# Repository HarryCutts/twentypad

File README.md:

# TwentyPad
TwentyPad is a simple twenty-key macro pad, that I built to learn about PCB design.

This repository contains the KiCAD project for PCB manufacture and assembly. The case was [designed
in Onshape][onshape-proj].

[onshape-proj]: https://cad.onshape.com/documents/e1701c21a3cb18f7b5686e27/w/70a0bcde95206762f85e44bf/e/dfee6d06467dfd7de2e80397

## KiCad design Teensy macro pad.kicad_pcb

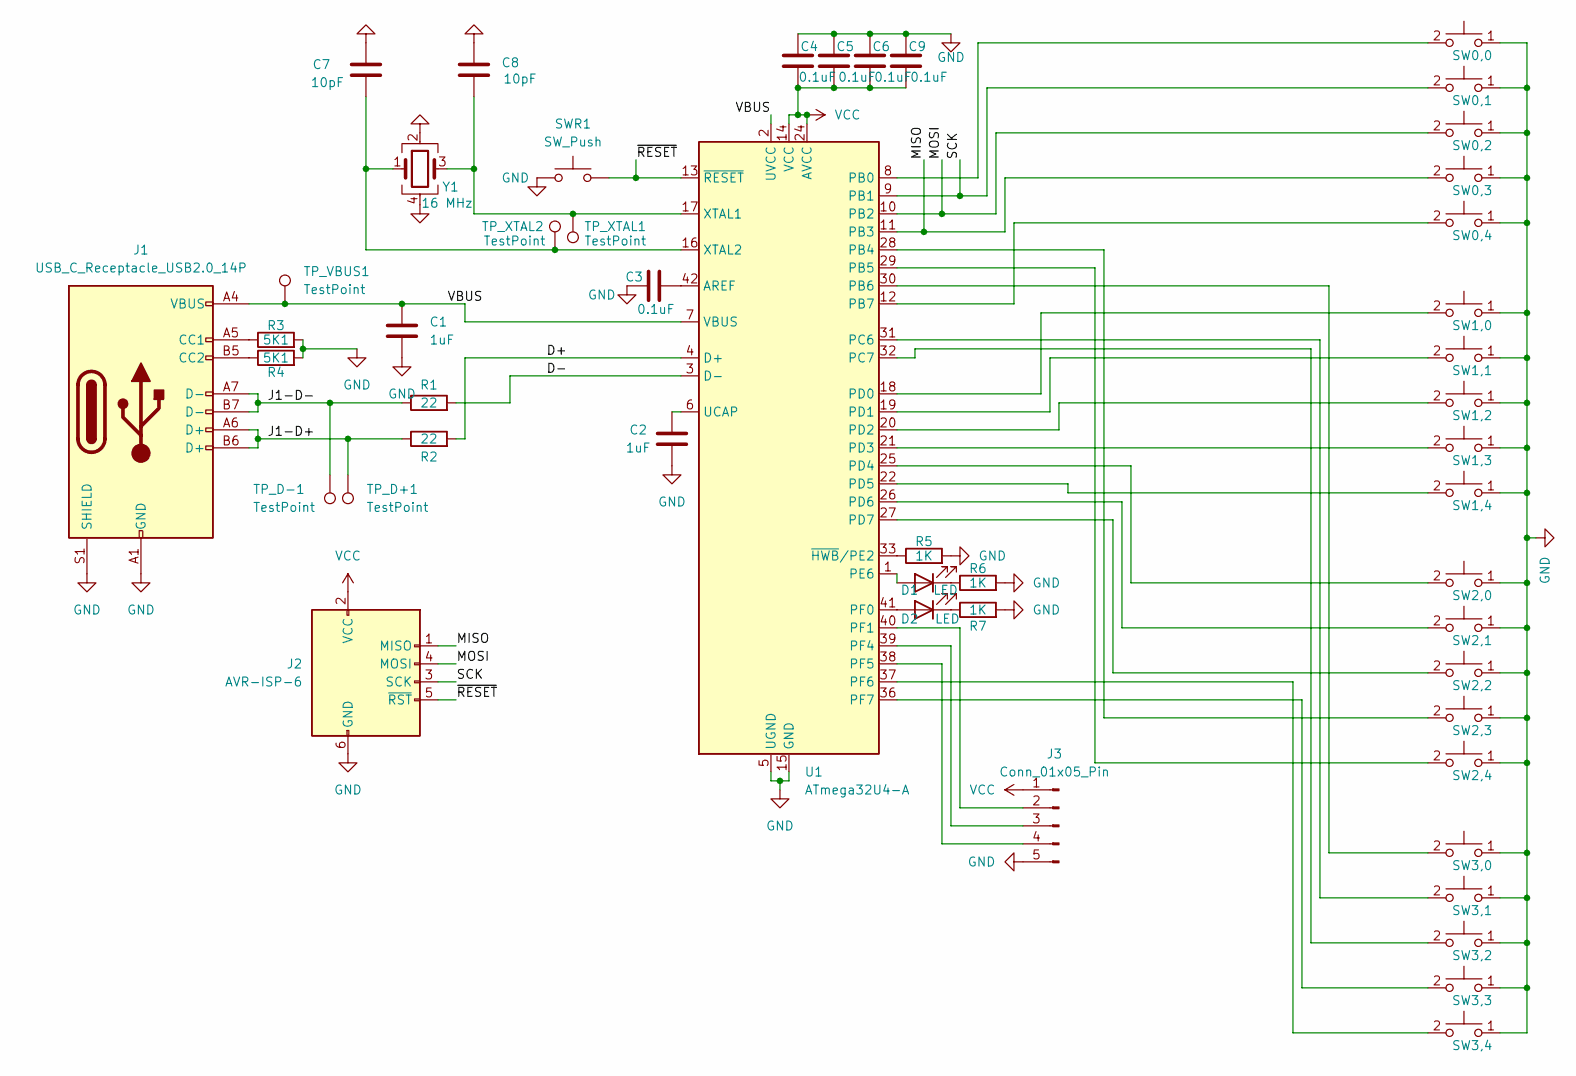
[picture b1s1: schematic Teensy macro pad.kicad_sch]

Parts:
C1, C2: 1uF; C_0805_2012Metric
C3, C4, C5, C6, C9: 0.1uF; C_0805_2012Metric
C7, C8: 10pF; C_0603_1608Metric
D1, D2: LED; LED_D5.0mm
J1: USB_C_Receptacle_USB2.0_14P; USB_C_Receptacle_HRO_TYPE-C-31-M-12
J2: AVR-ISP-6; IDC-Header_2x03_P2.54mm_Vertical
J3: Conn_01x05_Pin; PinHeader_1x05_P2.54mm_Vertical
R1, R2: 22; R_0805_2012Metric
R3, R4: 5K1; R_0805_2012Metric
R5, R6, R7: 1K; R_0805_2012Metric
SW0,0, SW0,1, SW0,2, SW0,3, SW0,4, SW1,0, SW1,1, SW1,2, SW1,3, SW1,4, SW2,0, SW2,1, SW2,2, SW2,3, SW2,4, SW3,0, SW3,1, SW3,2, SW3,3, SW3,4: CherryMX; SW_Cherry_MX_1.00u_PCB_with_bridge
SWR1: SW_Push; SW_Push_1P1T_XKB_TS-1187A
TP_D+1: TestPoint; TestPoint_Pad_D2.0mm
TP_D-1: TestPoint; TestPoint_Pad_D2.0mm
TP_VBUS1: TestPoint; TestPoint_Pad_D2.0mm
TP_XTAL1, TP_XTAL2: TestPoint; TestPoint_Pad_D2.0mm
U1: ATmega32U4-A; TQFP-44_10x10mm_P0.8mm
Y1: 16 MHz; Crystal_SMD_3225-4Pin_3.2x2.5mm

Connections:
/D+: R2.2, U1.4 (D+)
/D-: R1.2, U1.3 (D-)
/J1-D+: J1.A6 (D+), J1.B6 (D+), R2.1, TP_D+1.1
/J1-D-: J1.A7 (D-), J1.B7 (D-), R1.1, TP_D-1.1
/MISO: J2.1 (MISO), SW0,3.2, U1.11 (PB3)
/MOSI: J2.4 (MOSI), SW0,2.2, U1.10 (PB2)
/SCK: J2.3 (SCK), SW0,1.2, U1.9 (PB1)
/VBUS: C1.1, J1.A4 (VBUS), J1.A9 (VBUS), J1.B4 (VBUS), J1.B9 (VBUS), TP_VBUS1.1, U1.2 (UVCC), U1.7 (VBUS)
/~RESET: J2.5 (~RST), SWR1.2, U1.13 (~RESET)
GND: C1.2, C2.2, C3.1, C4.2, C5.2, C6.2, C7.1, C8.1, C9.2, J1.A1 (GND), J1.A12 (GND), J1.B1 (GND), J1.B12 (GND), J1.S1 (SHIELD), J2.6 (GND), J3.5, R3.2, R4.2, R5.2, R6.2, R7.2, SW0,0.1, SW0,1.1, SW0,2.1, SW0,3.1, SW0,4.1, SW1,0.1, SW1,1.1, SW1,2.1, SW1,3.1, SW1,4.1, SW2,0.1, SW2,1.1, SW2,2.1, SW2,3.1, SW2,4.1, SW3,0.1, SW3,1.1, SW3,2.1, SW3,3.1, SW3,4.1, SWR1.1, U1.5 (UGND), U1.15 (GND), U1.23 (GND), U1.35 (GND), U1.43 (GND), Y1.2, Y1.4
unnamed: D1.2 (A), U1.1 (PE6)
unnamed: D1.1 (K), R6.1
unnamed: D2.2 (A), U1.41 (PF0)
unnamed: D2.1 (K), R7.1
unnamed: J1.A5 (CC1), R3.1
unnamed: J1.B5 (CC2), R4.1
unnamed: J3.2, U1.40 (PF1)
unnamed: J3.3, U1.39 (PF4)
unnamed: J3.4, U1.38 (PF5)
unnamed: C3.2, U1.42 (AREF)
unnamed: SW0,0.2, U1.8 (PB0)
unnamed: SW2,3.2, U1.28 (PB4)
unnamed: SW2,4.2, U1.29 (PB5)
unnamed: SW3,0.2, U1.30 (PB6)
unnamed: SW0,4.2, U1.12 (PB7)
unnamed: SW3,1.2, U1.31 (PC6)
unnamed: SW3,2.2, U1.32 (PC7)
unnamed: SW1,0.2, U1.18 (PD0)
unnamed: SW1,1.2, U1.19 (PD1)
unnamed: SW1,2.2, U1.20 (PD2)
unnamed: SW1,3.2, U1.21 (PD3)
unnamed: SW2,0.2, U1.25 (PD4)
unnamed: SW1,4.2, U1.22 (PD5)
unnamed: SW2,1.2, U1.26 (PD6)
unnamed: SW2,2.2, U1.27 (PD7)
unnamed: SW3,4.2, U1.37 (PF6)
unnamed: SW3,3.2, U1.36 (PF7)
unnamed: C2.1, U1.6 (UCAP)
unnamed: C8.2, TP_XTAL1.1, U1.17 (XTAL1), Y1.3
unnamed: C7.2, TP_XTAL2.1, U1.16 (XTAL2), Y1.1
unnamed: R5.1, U1.33 (~HWB/PE2)
VCC: C4.1, C5.1, C6.1, C9.1, J2.2 (VCC), J3.1, U1.14 (VCC), U1.24 (AVCC), U1.34 (VCC), U1.44 (AVCC)

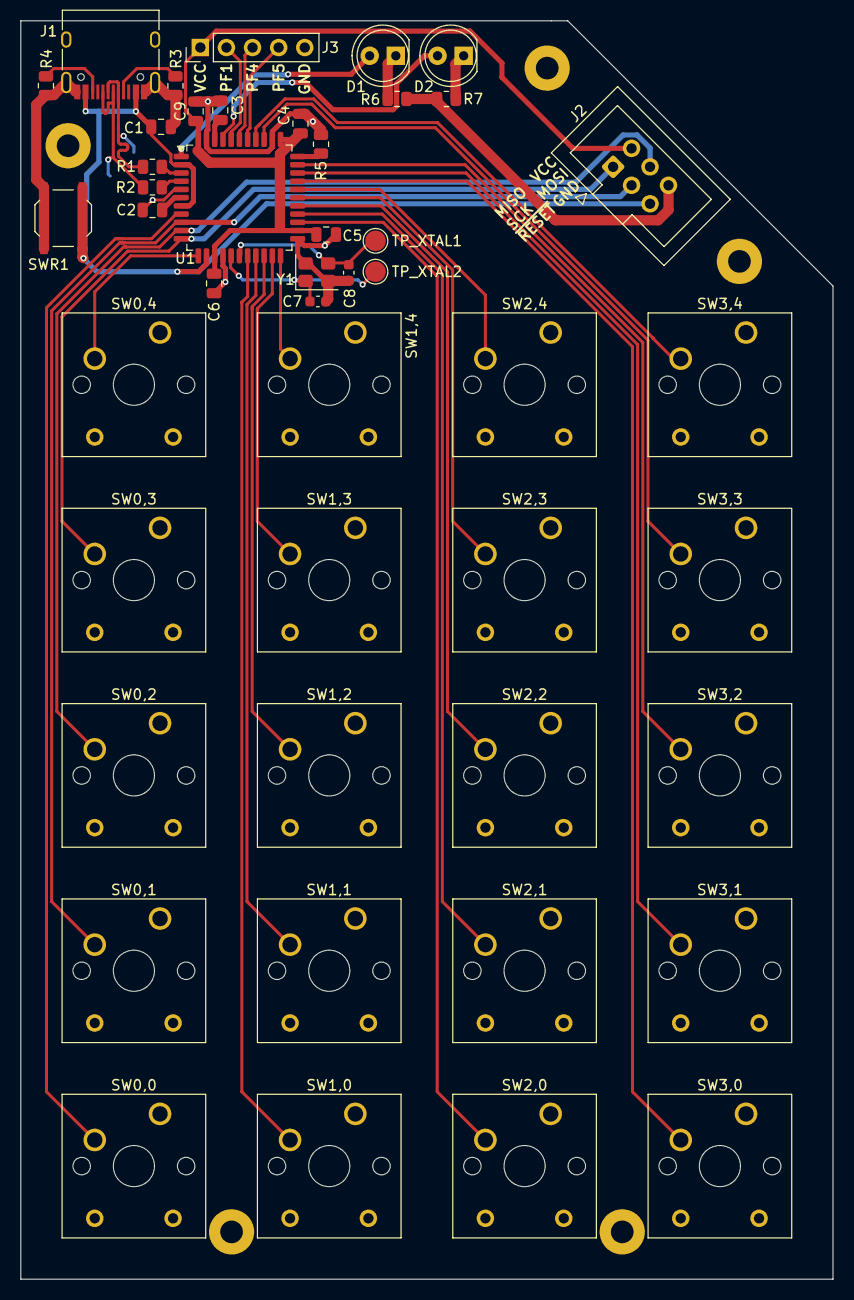
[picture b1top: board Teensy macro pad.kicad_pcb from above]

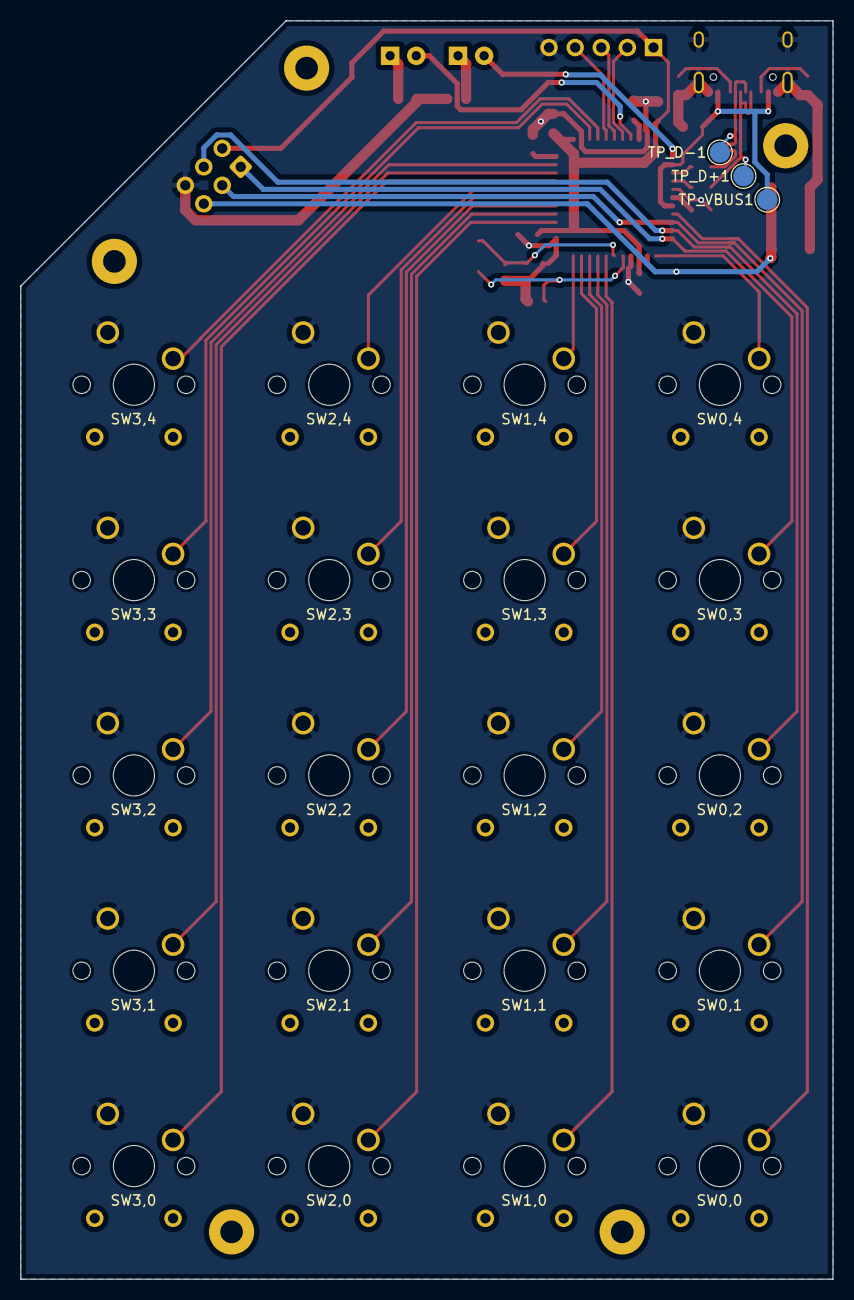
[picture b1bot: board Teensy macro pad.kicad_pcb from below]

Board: 2 copper layers, 79.0 x 122.4 mm, 54 parts (3 on the bottom side), 42 nets.

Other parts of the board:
HOLE1, HOLE2, HOLE3, HOLE4, HOLE5: MountingHole_2.2mm_M2_Pad

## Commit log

2025-06-28 Add partially-complete design with Teensy 2.0
2025-07-05 Switch to putting the chip on the board directly
2025-07-05 Load in JLCPCB capabilities and fix some violations
    I loaded the constraints from https://jlcpcb.com/capabilities/ into the
    board setup, then ran the DRC and fixed some of the issues (not all,
    since I need to do some re-arrangement anyway).
2025-07-06 Move decoupling capacitors to be one per VCC pin
    Pages 5 and 6 of AN2519 [0] are particularly relevant here.
    [0]: https://ww1.microchip.com/downloads/aemDocuments/documents/MCU08/ApplicationNotes/ApplicationNotes/AN2519-AVR-Microcontroller-Hardware-Design-Considerations-00002519B.pdf
2025-07-06 Add a decoupling capacitor to VCC pin 44
    This isn't on the Teensy, but AN2519 is quite clear that "For devices
    with multiple pairs of power and ground pins, it is essential that there
    is a decoupling capacitor for every pair of pins."
2025-07-14 Change and move USB-C connector footprint
    The old footprint was causing DRC errors (due to pads being too close to
    its holes). Replace it with the one Matthew recommends
    (...TYPE-C-31-M-12) and also move it so the edge of the connector
    overhangs the board edge to make it easier to put the board in a case or
    something.
2025-09-29 Fix some hole clearance errors
2025-09-29 Move some silkscreen labels
2025-09-29 Add test points for VBUS, XTAL1, and XTAL2
2025-10-04 Add holes for bridge pins on the switches
    The switches I intend to use for the project have two extra pins in the
    bottom corners, which are simply bridged together. Rather than cut them
    off, it seems like a good opportunity to try customizing a footprint, so
    create a modified footprint which adds holes for the pins. The Cherry MX
    datasheet [0] provided pin locations and recommended hole dimensions.
    [0]: https://cdn.sparkfun.com/datasheets/Components/Switches/MX%20Series.pdf
2025-10-06 Add rear silkscreen labels for switches
2025-10-13 Add mounting holes
2025-10-13 Update MCU footprint
2025-10-13 Add JLCPCB part numbers
    C7 and C8 (10pF capacitors) had to be changed to a smaller 0603
    footprint, so that I could use parts on the basic JLCPCB parts list.
2025-10-20 Add labels and improve silkscreens
    Capacitors and resistors now follow the rule that their silkscreen label
    should be in the same orientation as the component. Also added labels
    for pin headers, and a copyright notice and GitHub link to the back.
2025-10-20 Add USB test points
2025-10-27 Rename reset switch symbol
    Having a switch with reference SW1 as well as ones with SW1,0 to SW1,4
    seemed to confuse Fabrication Toolkit or JLCPCB's BOM processor.
2025-12-01 Add a 3D model for the switches
    This should make KiCAD's exported model more useful for case design.
2026-05-11 Untrack fp-info-cache
2026-05-11 Add README and photo
2026-05-11 Fix link in README

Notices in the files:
Teensy macro pad.kicad_pcb:
© Harry Cutts 2025
